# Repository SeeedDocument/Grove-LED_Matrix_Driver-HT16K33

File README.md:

# Grove-LED_Matrix_Driver-HT16K33

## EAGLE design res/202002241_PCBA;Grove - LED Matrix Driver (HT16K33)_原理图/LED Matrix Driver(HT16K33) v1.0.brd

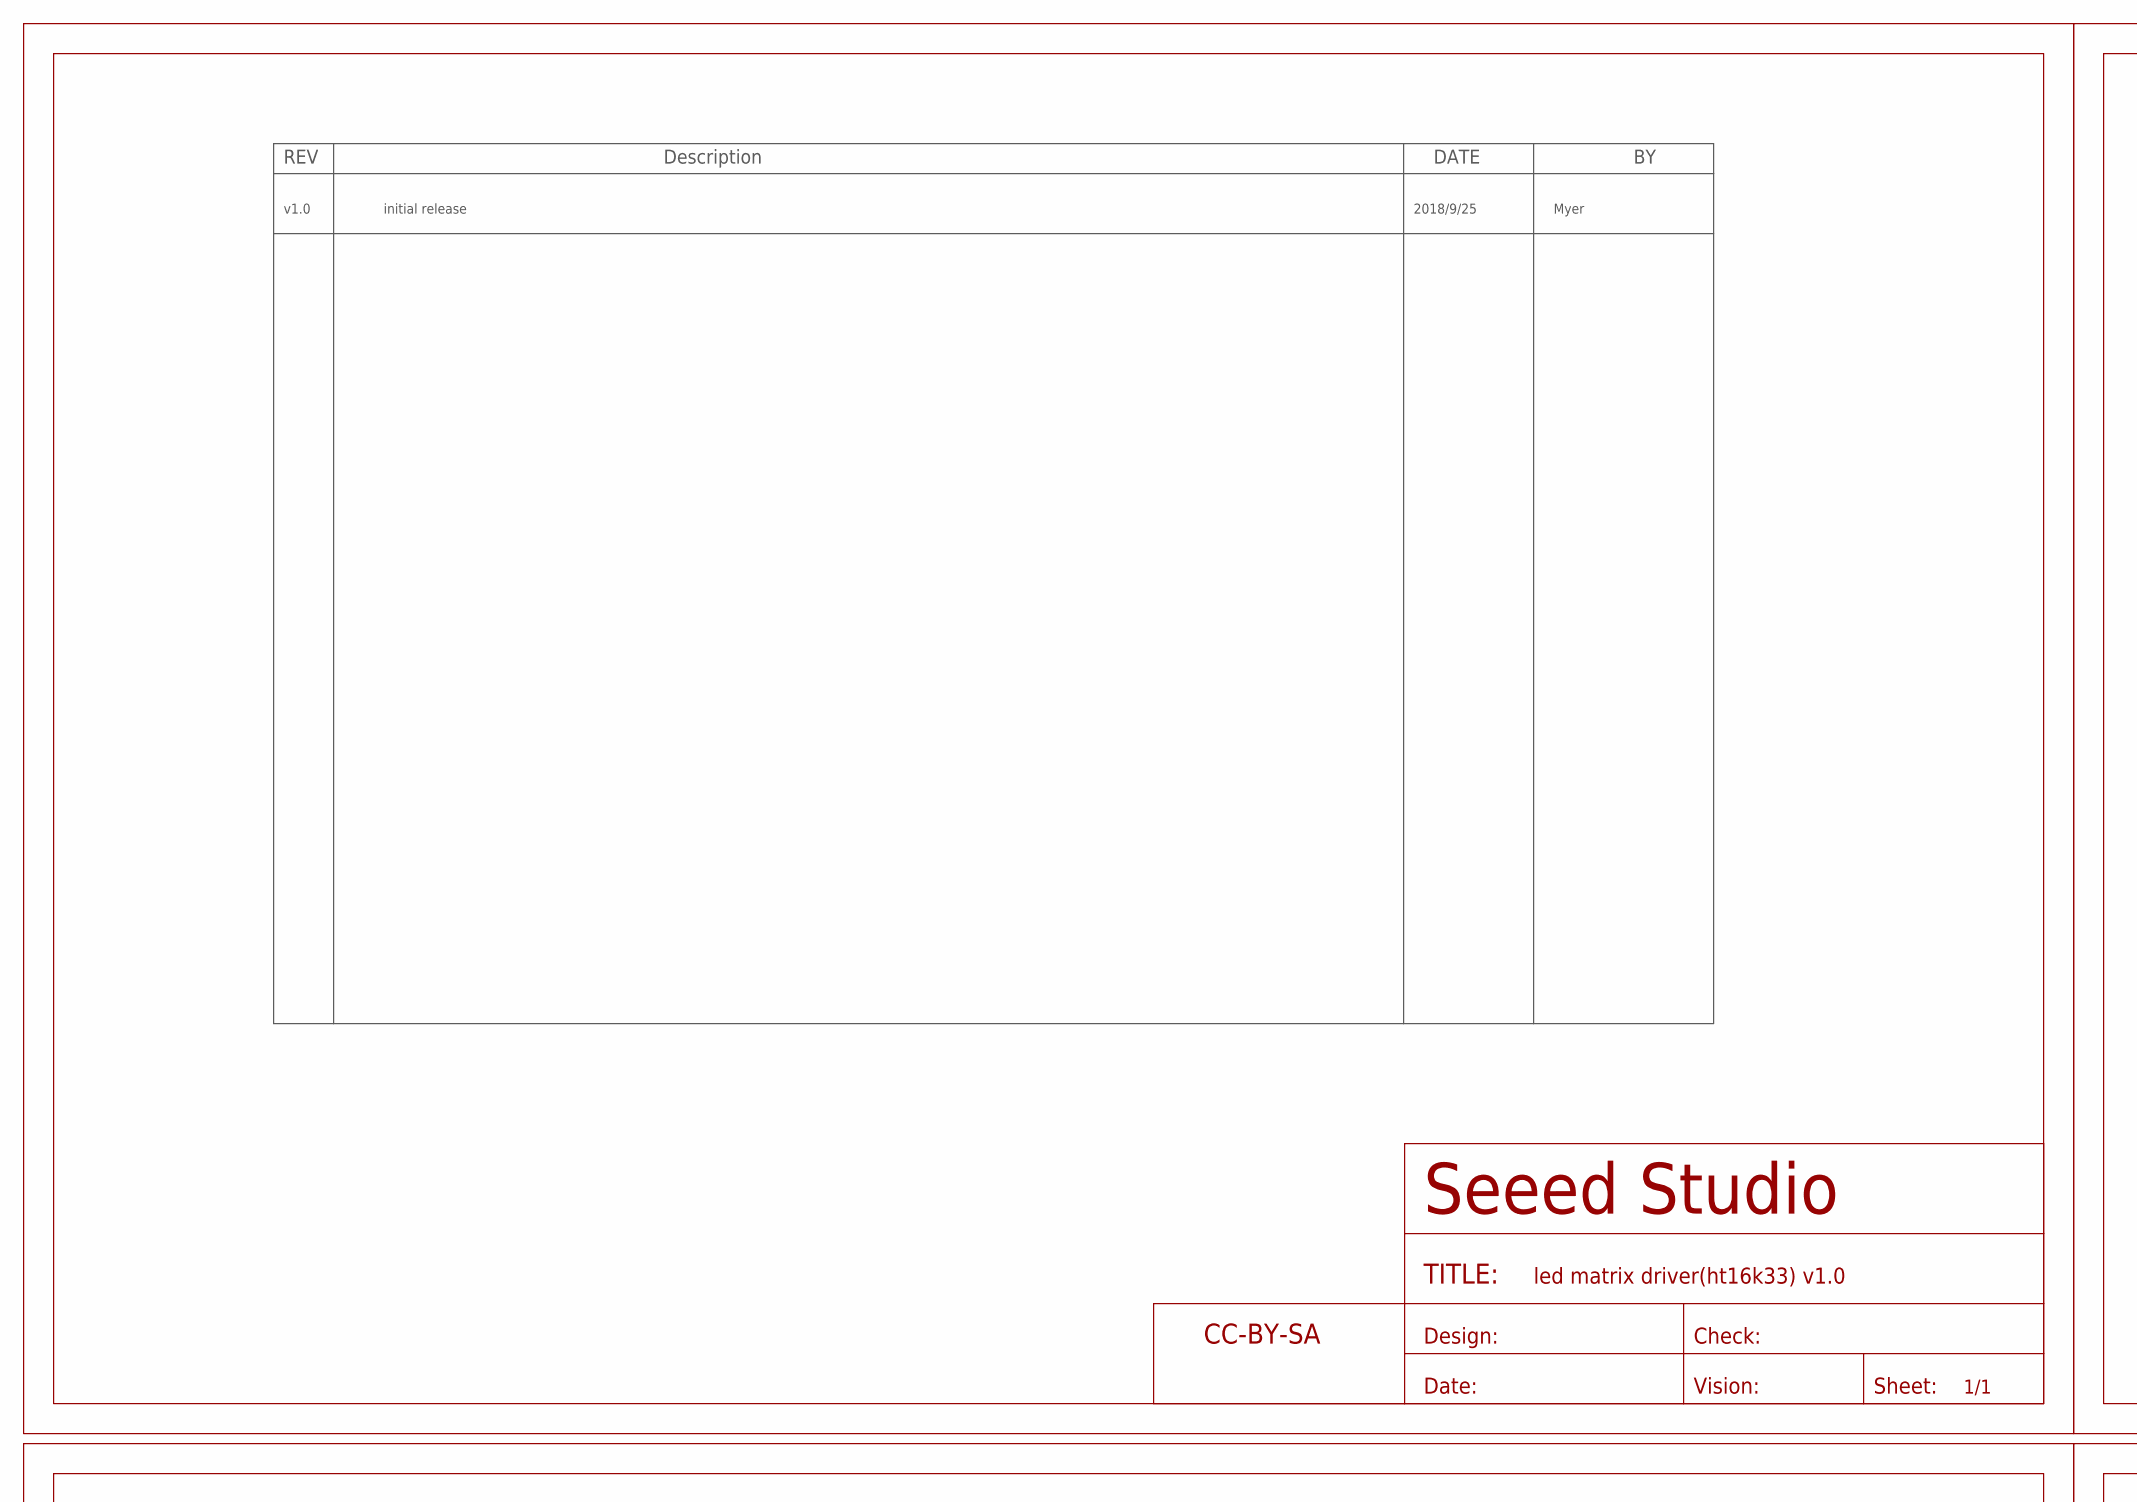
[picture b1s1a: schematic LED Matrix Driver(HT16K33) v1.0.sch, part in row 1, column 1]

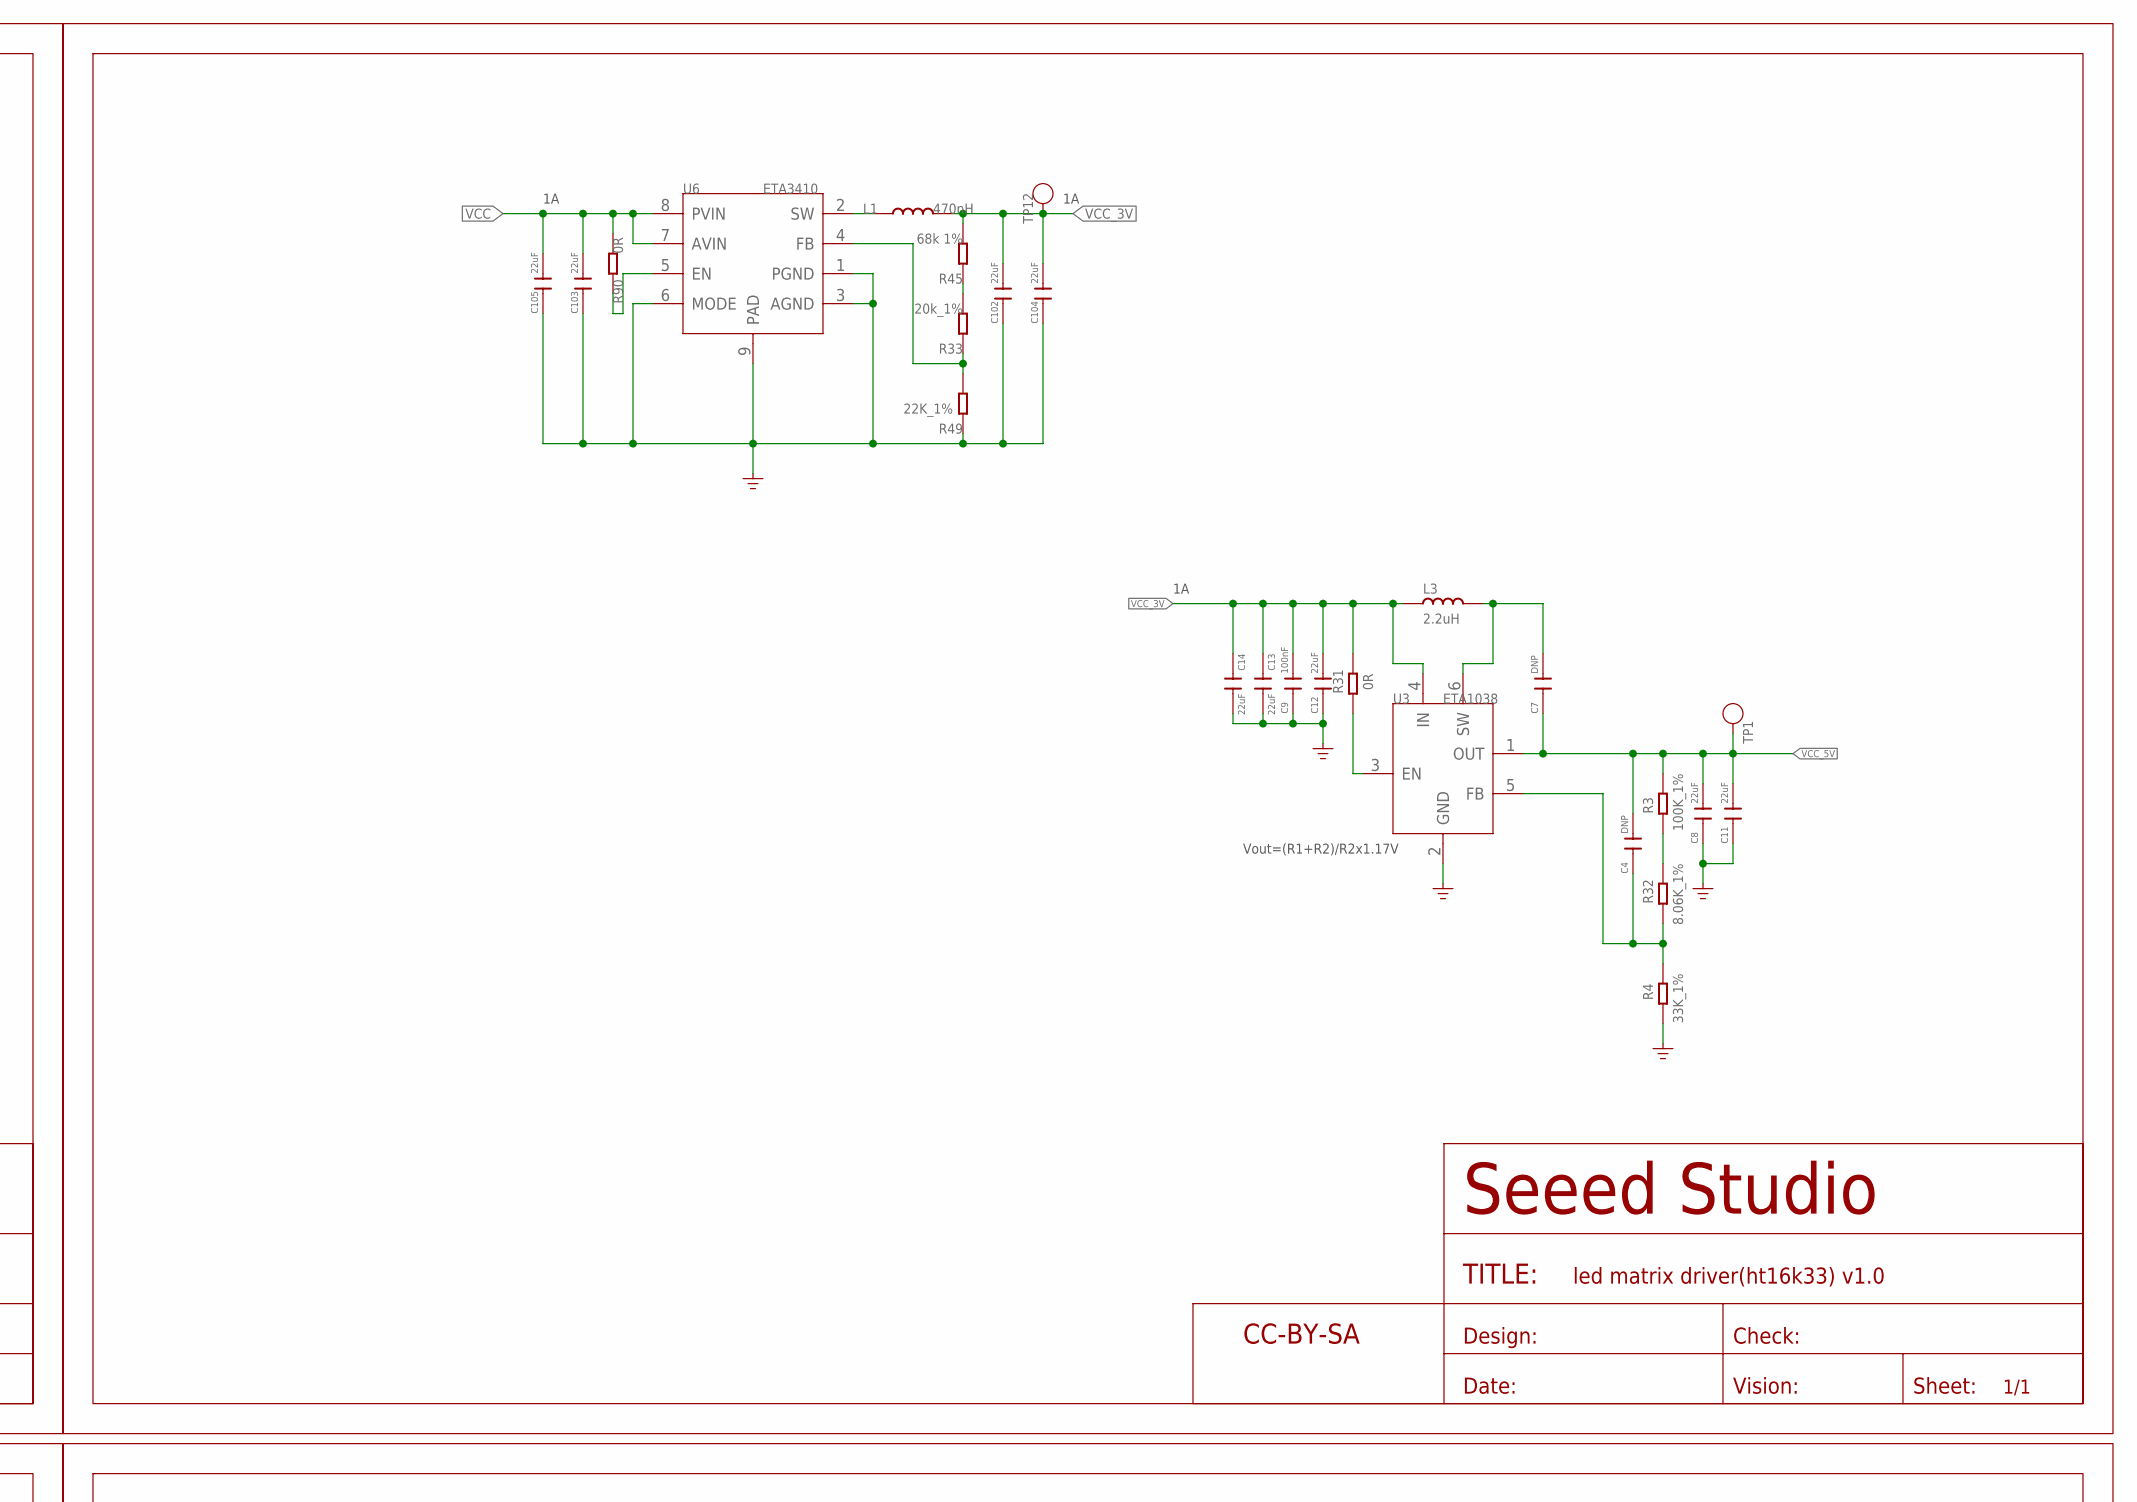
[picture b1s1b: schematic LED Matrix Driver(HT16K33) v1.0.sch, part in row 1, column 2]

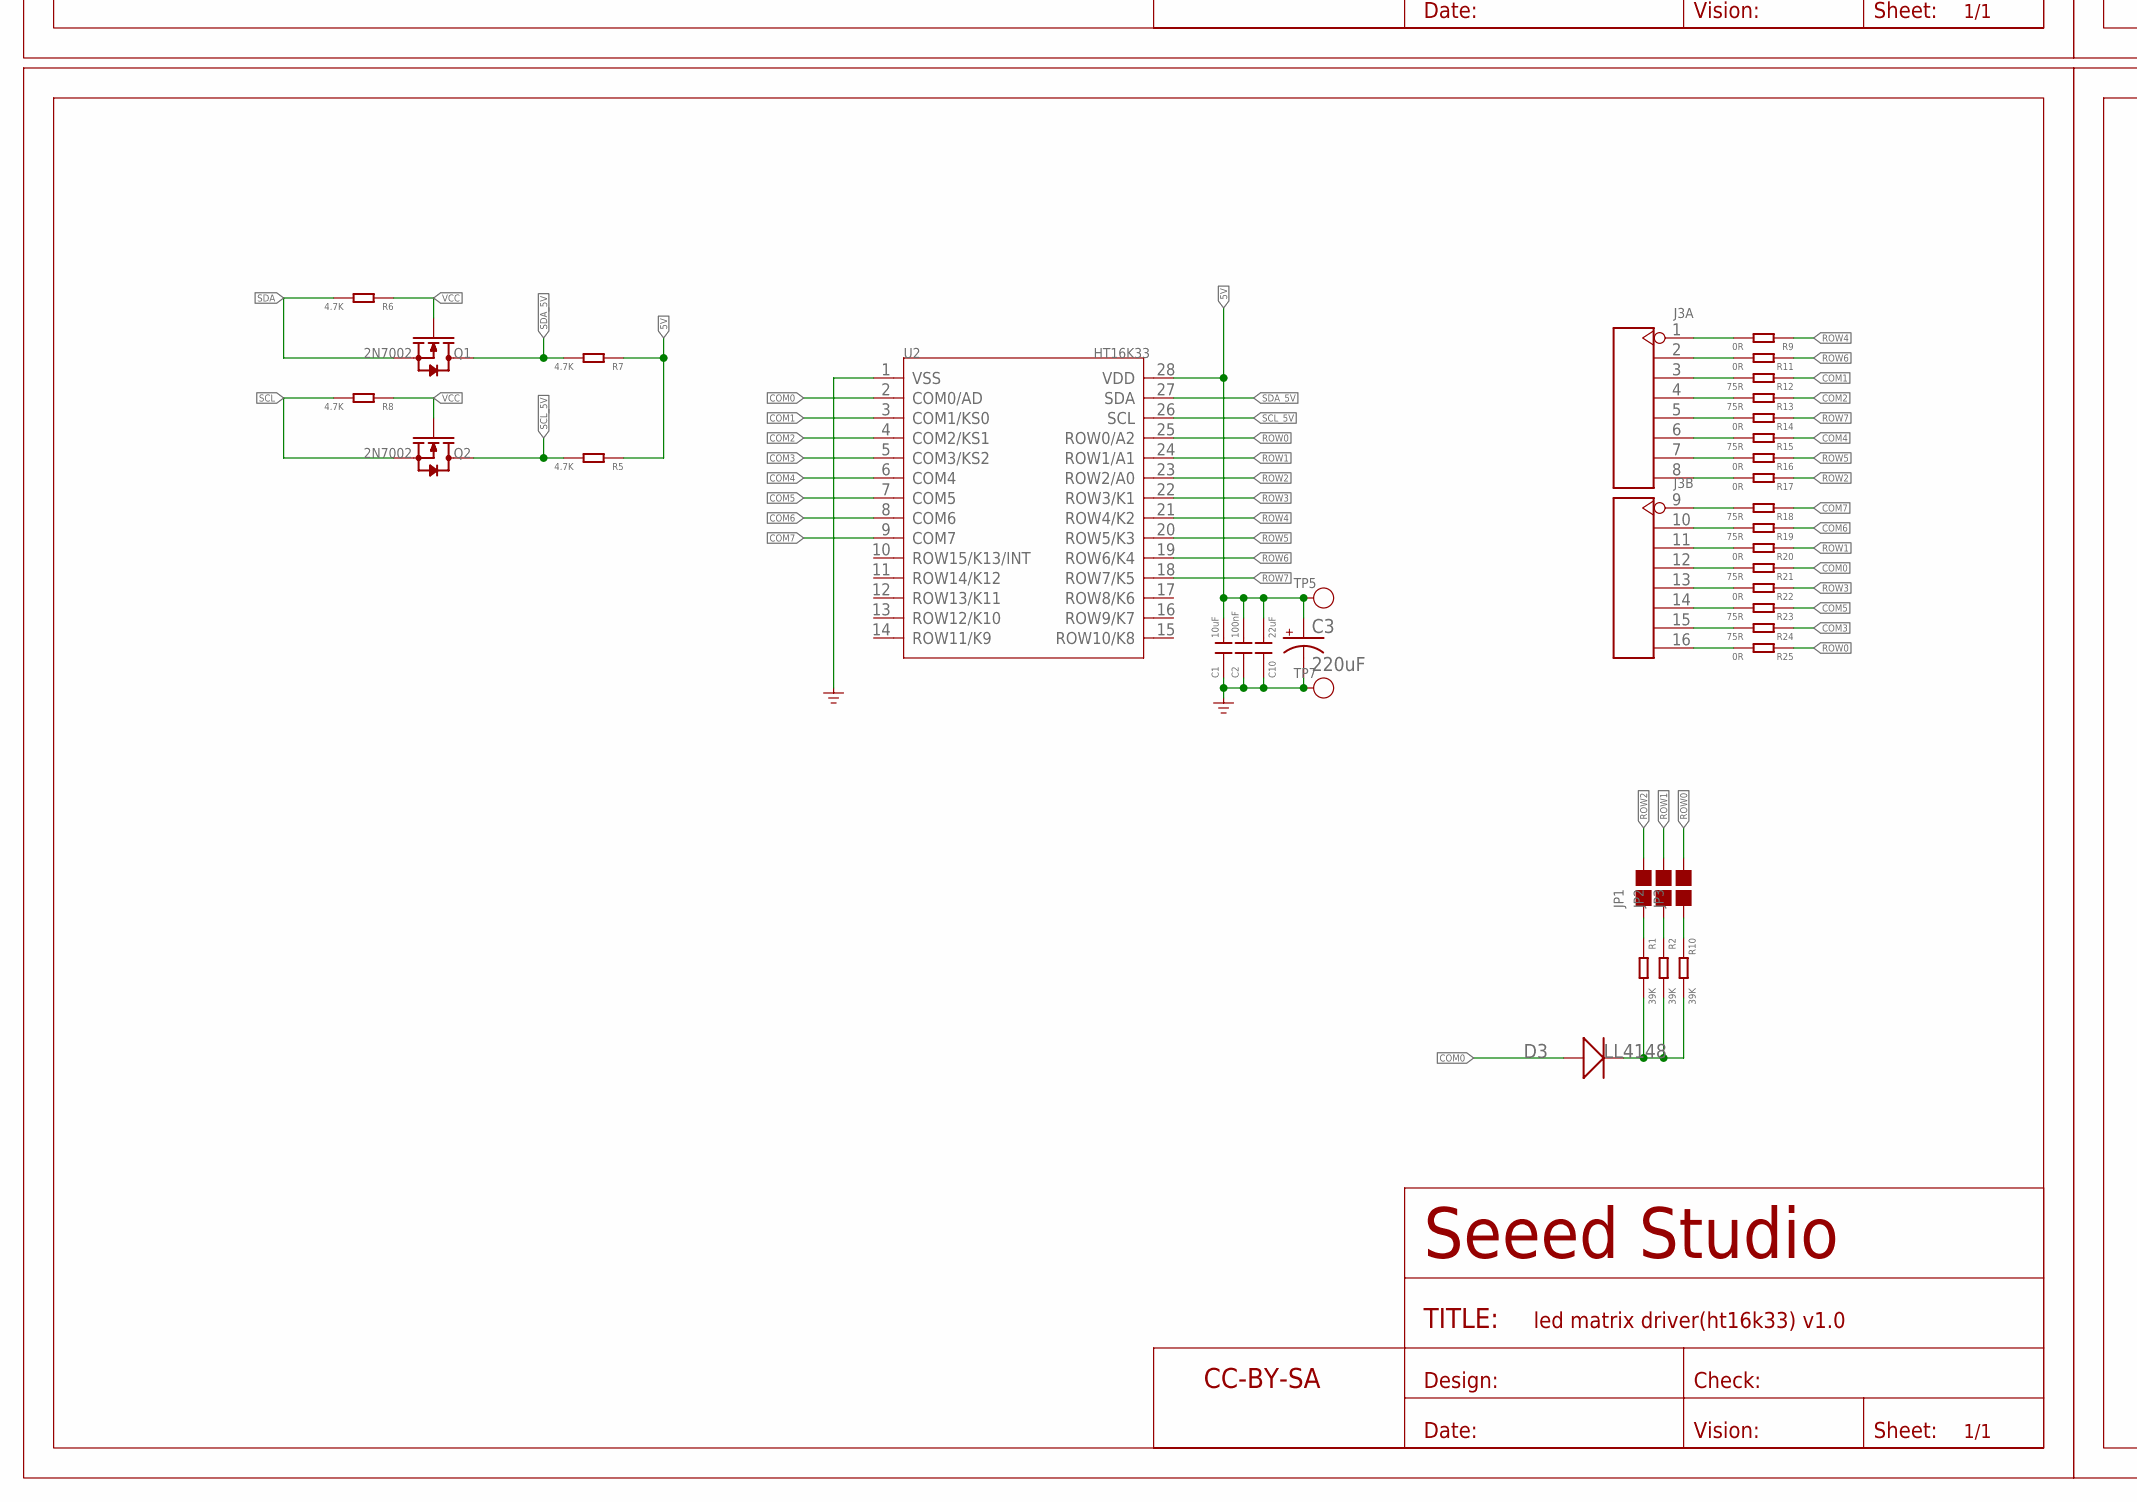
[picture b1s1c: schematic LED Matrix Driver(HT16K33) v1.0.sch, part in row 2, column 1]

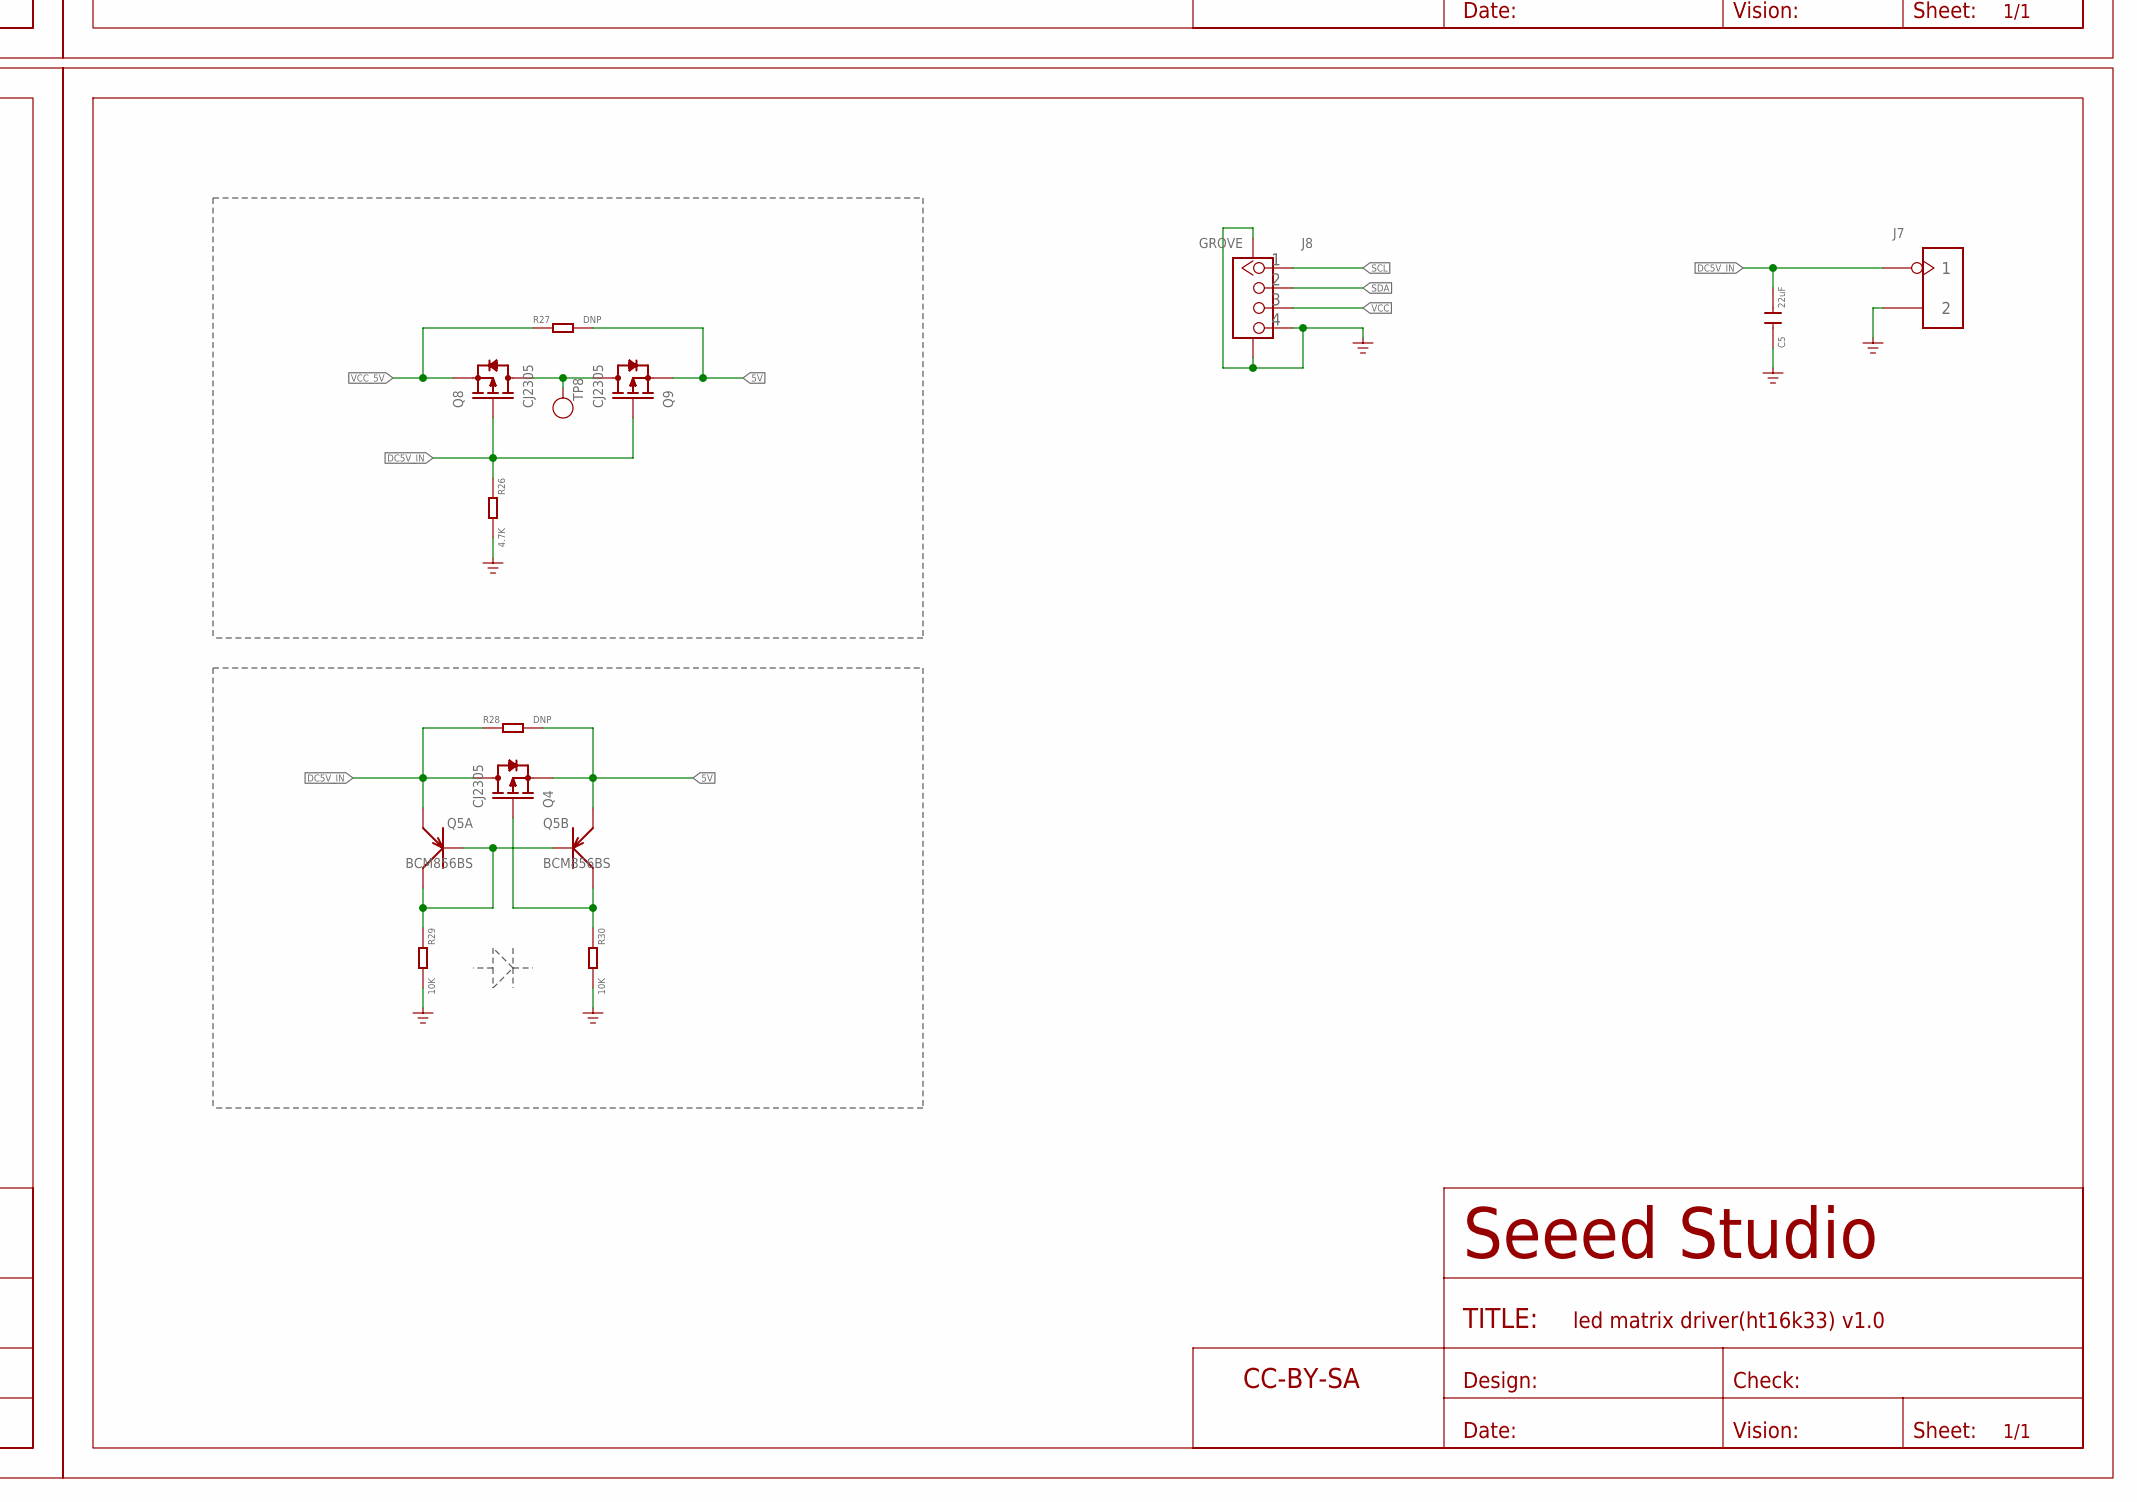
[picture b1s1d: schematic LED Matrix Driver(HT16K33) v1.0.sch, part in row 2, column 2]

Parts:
C1: 10uF; C0805
C2, C9: 100nF; C0603
C3: 220uF; PANASONIC_D
C4, C7: DNP; C0603
C5, C10: 22uF; C0805
C8, C11, C12, C13, C14, C102, C103, C104, C105: 22uF; C0603
D3: LL4148; DO-35-SMD
FR1, FR2, FR3: SEEEDSTUDIO-OPEN-SCH-FRAME; SEEEDSTUDIO-PCB-FRAME
J3: HEADER-1X8PX2-LED-28.5MM; H8X2-SMD-2.54-28.5MM
J7: HEADER-2P-65/35MIL; H2-2.54
J8: GROVE; HW4-SMD-2.0
JP1, JP2, JP3: JP-2P-NO; 2P-SMD-NO
L1: 470nH; L201610
L3: 2.2uH; L0806
Q1, Q2: 2N7002; SOT-23
Q4, Q8, Q9: CJ2305; SOT-23
Q5: BCM856BS; SOT-363
R1, R2, R10: 39K; R0603
R3: 100K_1%; R0603
R4: 33K_1%; R0603
R5, R6, R7, R8, R26: 4.7K; R0603
R9, R11, R14, R16, R17, R20, R22, R25, R31, R90: 0R; R0603
R12, R13, R15, R18, R19, R21, R23, R24: 75R; R0603
R27, R28: DNP; R0603
R29, R30: 10K; R0603
R32: 8.06K_1%; R0603
R33: 20k_1%; R0603
R45: 68k 1%; R0603
R49: 22K_1%; R0603
TP1, TP5, TP7, TP8, TP12: TEST-POINT'4545'; TP-D45MIL
U2: HT16K33; SOP28-1.27-18.2X7.4MM
U3: ETA1038; SOT-23-6
U6: ETA3410; DFN8G-0.5-2X2MM
U$1: SEEEDSTUDIO-OPEN-SCH-FRAME; SEEEDSTUDIO-PCB-FRAME

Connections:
5V: C1.2, C2.2, C3.+, C10.2, Q4.2 (S), Q5.4 (E), Q9.2 (S), R5.1, R7.1, R27.2, R28.2, TP5.T, U2.28 (VDD)
COM0: D3.A (+), R21.1, U2.2 (COM0/AD)
COM1: R12.1, U2.3 (COM1/KS0)
COM2: R13.1, U2.4 (COM2/KS1)
COM3: R24.1, U2.5 (COM3/KS2)
COM4: R15.1, U2.6 (COM4)
COM5: R23.1, U2.7 (COM5)
COM6: R19.1, U2.8 (COM6)
COM7: R18.1, U2.9 (COM7)
DC5V_IN: C5.2, J7.1, Q4.3 (D), Q5.1 (E), Q8.1 (G), Q9.1 (G), R26.1, R28.1
GND: C1.1, C2.1, C3.-, C5.1, C8.1, C9.1, C10.1, C11.1, C12.1, C13.2, C14.2, C102.1, C103.1, C104.1, C105.1, J7.2, J8.4, J8.SS1, J8.SS2, R4.1, R26.2, R29.2, R30.2, R49.1, TP7.T, U2.1 (VSS), U3.2 (GND), U6.1 (PGND), U6.3 (AGND), U6.6 (MODE), U6.9 (PAD)
unnamed: D3.C (-), R1.2, R2.2, R10.2
unnamed: JP1.1, R1.1
unnamed: L1.1, U6.2 (SW)
unnamed: R90.1, U6.5 (EN)
unnamed: J3.1, R9.2
unnamed: JP2.1, R2.1
unnamed: JP3.1, R10.1
unnamed: R33.2, R45.1
unnamed: J3.2, R11.2
unnamed: Q5.2 (B), Q5.5 (B), Q5.6 (C), R29.1
unnamed: J3.3, R12.2
unnamed: Q4.1 (G), Q5.3 (C), R30.1
unnamed: J3.4, R13.2
unnamed: J3.5, R14.2
unnamed: J3.6, R15.2
unnamed: J3.7, R16.2
unnamed: J3.8, R17.2
unnamed: J3.9 (1), R18.2
unnamed: J3.10 (2), R19.2
unnamed: J3.11 (3), R20.2
unnamed: J3.12 (4), R21.2
unnamed: J3.13 (5), R22.2
unnamed: J3.14 (6), R23.2
unnamed: J3.15 (7), R24.2
unnamed: J3.16 (8), R25.2
unnamed: C7.2, L3.2, U3.6 (SW)
unnamed: Q8.3 (D), Q9.3 (D), TP8.T
unnamed: C4.1, R4.2, R32.2, U3.5 (FB)
unnamed: R31.2, U3.3 (EN)
unnamed: R3.2, R32.1
unnamed: R33.1, R49.2, U6.4 (FB)
ROW0: JP3.2, R25.1, U2.25 (ROW0/A2)
ROW1: JP2.2, R20.1, U2.24 (ROW1/A1)
ROW2: JP1.2, R17.1, U2.23 (ROW2/A0)
ROW3: R22.1, U2.22 (ROW3/K1)
ROW4: R9.1, U2.21 (ROW4/K2)
ROW5: R16.1, U2.20 (ROW5/K3)
ROW6: R11.1, U2.19 (ROW6/K4)
ROW7: R14.1, U2.18 (ROW7/K5)
SCL: J8.1, Q2.2 (S), R8.2
SCL_5V: Q2.3 (D), R5.2, U2.26 (SCL)
SDA: J8.2, Q1.2 (S), R6.2
SDA_5V: Q1.3 (D), R7.2, U2.27 (SDA)
VCC: C103.2, C105.2, J8.3, Q1.1 (G), Q2.1 (G), R6.1, R8.1, R90.2, U6.7 (AVIN), U6.8 (PVIN)
VCC_3V: C9.2, C12.2, C13.1, C14.1, C102.2, C104.2, L1.2, L3.1, R31.1, R45.2, TP12.T, U3.4 (IN)
VCC_5V: C4.2, C7.1, C8.2, C11.2, Q8.2 (S), R3.1, R27.1, TP1.T, U3.1 (OUT)

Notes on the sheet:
Vout=(R1+R2)/R2x1.17V
initial release
v1.0
2018/9/25
Myer

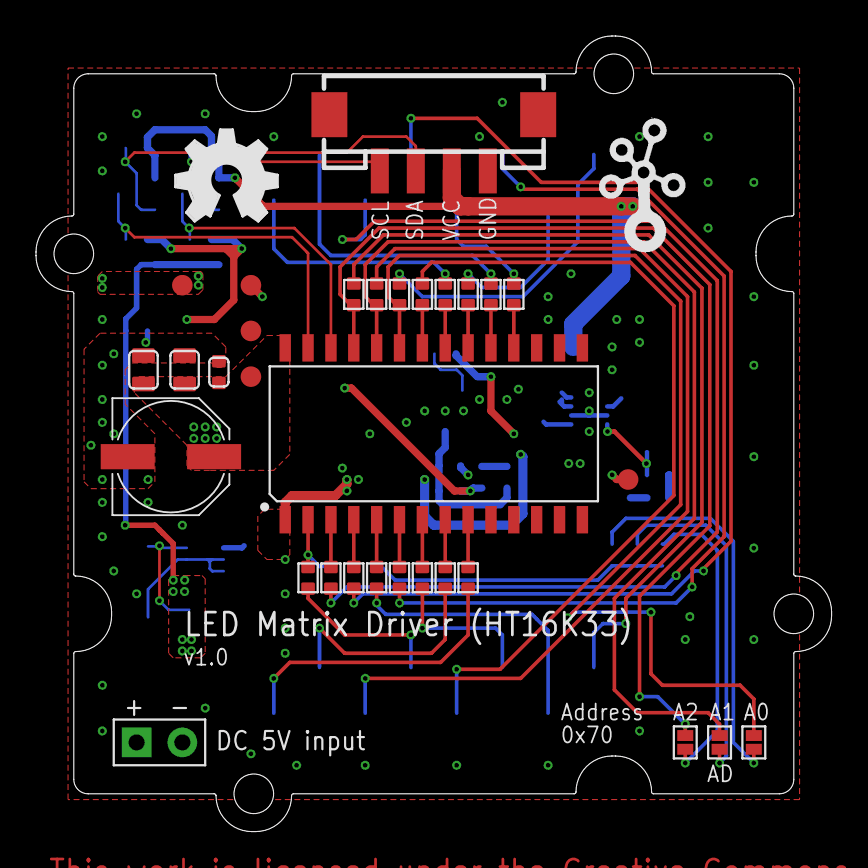
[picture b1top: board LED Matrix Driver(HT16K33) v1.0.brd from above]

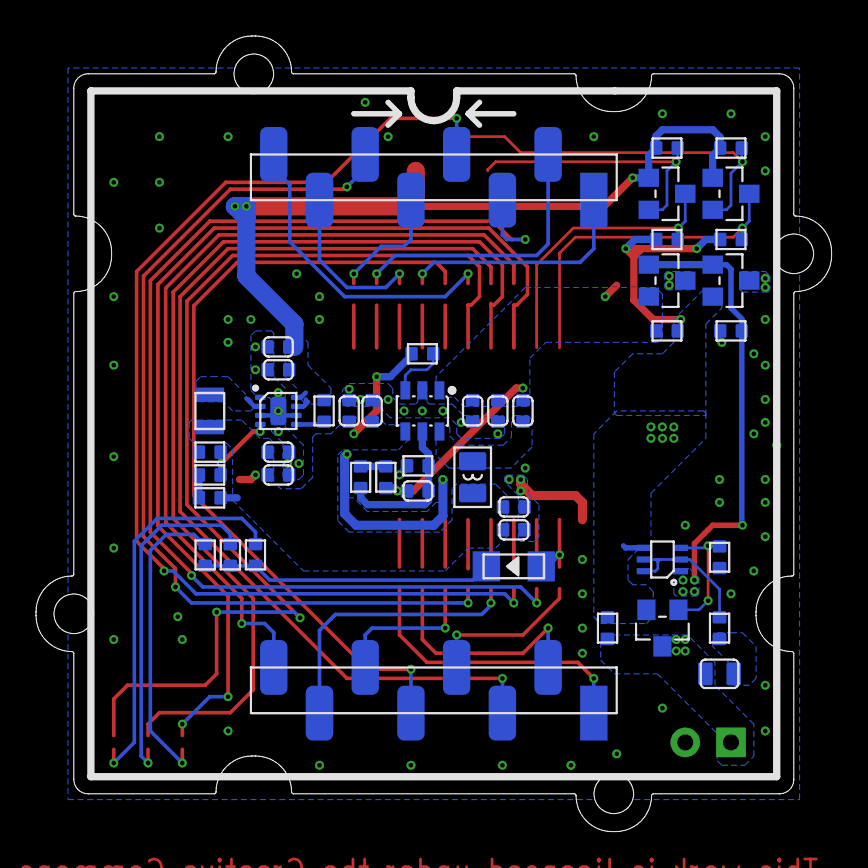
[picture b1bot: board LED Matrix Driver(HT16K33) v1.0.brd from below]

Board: 2 copper layers, 44.2 x 44.2 mm, 83 parts (45 on the bottom side), 57 nets.

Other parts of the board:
U$3: 2X2U-DIM-W/-DRILL
U$4: OSHW_FILLX200_NOTEXT
U$5: TWIGLOGO

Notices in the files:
parts and their libraries:
moudle-new: This work is licensed under the Creative Commons Attribution 4.0 International License.
To view a copy of this license,visit:
http://creativecommons.org/licenses/by-sa/4.0
moudle-new: CC-BY-SA
